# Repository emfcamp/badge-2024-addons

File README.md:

# EMF Badge Addons

Welcome!  This is the place to share your addons for the EMF 2024+ Badges.

## Addon submission rules

- Addons need to follow the top-level folder structure: `your_handle/addon_name/`
- We recommend you split your addon inside this folder into hardware and software (if needed) directories
- The top level of your addon folder should contain a README.md file, with a short description of the addon
- The top level of your addon folder should contain a photograph / render of your addon, in jpg or png format
- Addons in this repository are goverened by the repository license: CERN OHL Permissive. If you do not agree with this license, please don't submit your addon here.
- If your addon is a hexpansion, put hexpansion in the name so others can find it!

To submit your addon, open a pull request and we'll get it merged ASAP.  Pull requests will be minimally reviewed, mainly to make sure the rules are being followed.  Generally any update-PRs to a user's directory from that user will be accepted without much review.

Please don't make us make any more rules :D

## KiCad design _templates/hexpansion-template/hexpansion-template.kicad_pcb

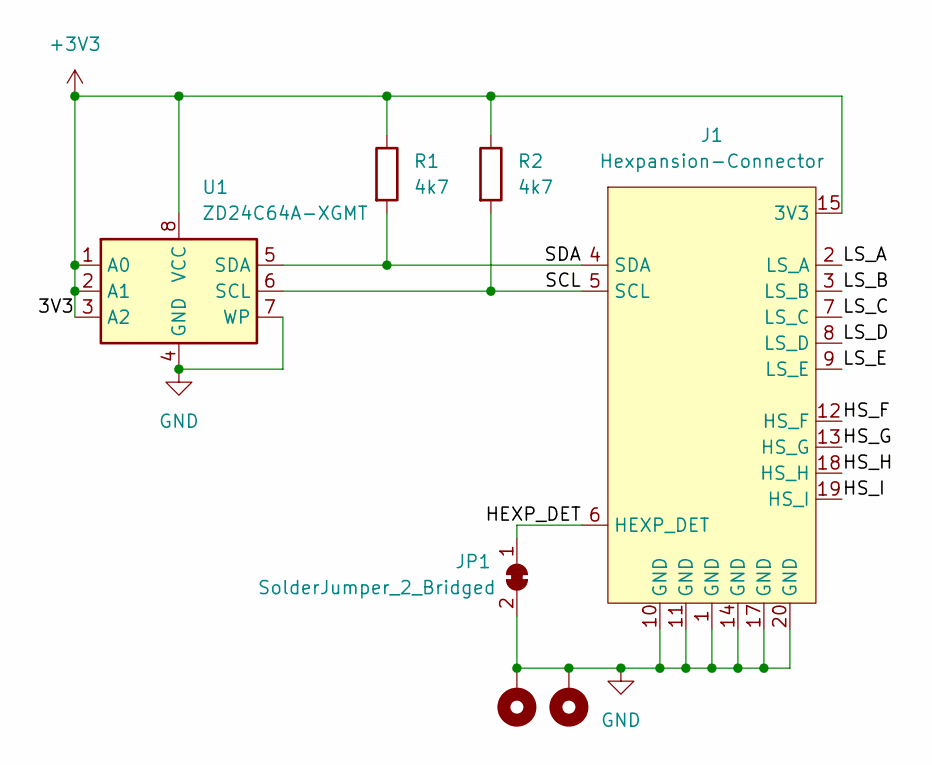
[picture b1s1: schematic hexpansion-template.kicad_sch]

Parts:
H1, H2: MountingHole_Pad; MountingHole_2.2mm_M2_Pad_Via
J1: Hexpansion-Connector; hexpansion-edge-connector
JP1: SolderJumper_2_Bridged; SolderJumper-2_P1.3mm_Bridged_RoundedPad1.0x1.5mm
R1, R2: 4k7; R_0402_1005Metric; MPN C5120109
U1: ZD24C64A-XGMT; TSSOP-8_4.4x3mm_P0.65mm; MPN C2875852

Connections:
+3V3: J1.15 (3V3), J1.16 (3V3), R1.1, R2.1, U1.1 (A0), U1.2 (A1), U1.3 (A2), U1.8 (VCC)
/HEXP_DET: J1.6 (HEXP_DET), JP1.1 (A)
/HS_F: J1.12 (HS_F)
/HS_G: J1.13 (HS_G)
/HS_H: J1.18 (HS_H)
/HS_I: J1.19 (HS_I)
/LS_A: J1.2 (LS_A)
/LS_B: J1.3 (LS_B)
/LS_C: J1.7 (LS_C)
/LS_D: J1.8 (LS_D)
/LS_E: J1.9 (LS_E)
/SCL: J1.5 (SCL), R2.2, U1.6 (SCL)
/SDA: J1.4 (SDA), R1.2, U1.5 (SDA)
GND: H1.1, H2.1, J1.1 (GND), J1.10 (GND), J1.11 (GND), J1.14 (GND), J1.17 (GND), J1.20 (GND), JP1.2 (B), U1.4 (GND), U1.7 (WP)

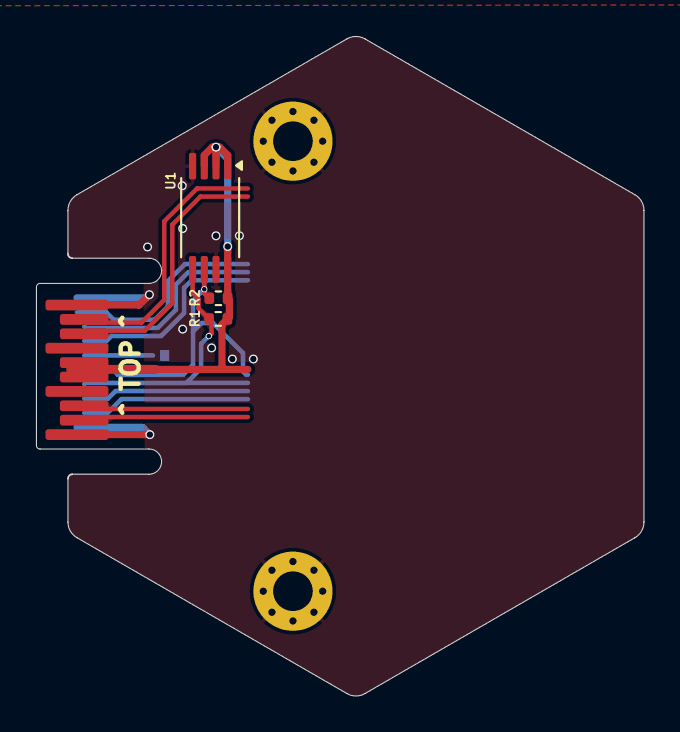
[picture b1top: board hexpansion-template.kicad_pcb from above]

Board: 2 copper layers, 33.7 x 36.6 mm, 7 parts (1 on the bottom side), 5 nets.

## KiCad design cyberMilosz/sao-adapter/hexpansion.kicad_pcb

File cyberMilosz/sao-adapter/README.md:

# SAOv2 / SAOv1.69bis hexpansion/hexdapter(?)

Provides power, `SDA`/`SCL` and exposes `LS_A`/`LS_B` as GPIO pins to your bog-standard [Simple Add-On](https://hackaday.io/project/175182-simple-add-ons-sao)/[Shitty Add-On](https://hackaday.com/2019/03/20/introducing-the-shitty-add-on-v1-69bis-standard/)

If everything goes to plan (does it ever?), this board should unleash the "power" of SAOs in the Tildragon.

wow!

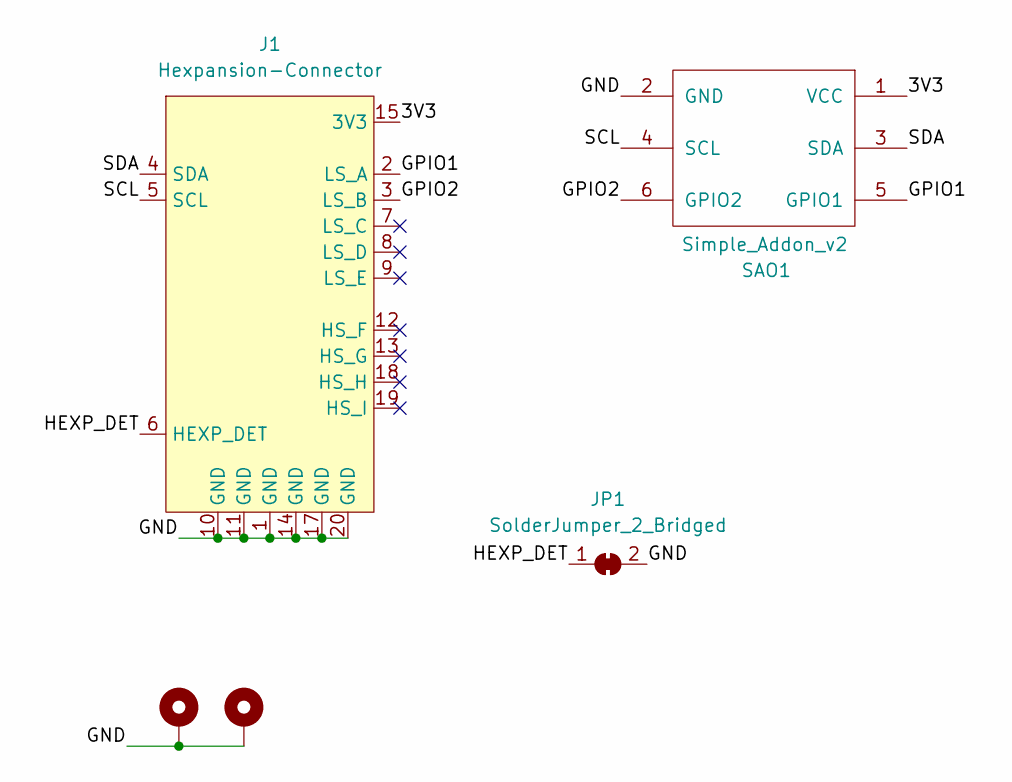
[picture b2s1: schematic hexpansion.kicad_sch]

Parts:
H1, H2: MountingHole_Pad; MountingHole_2.2mm_M2_Pad_Via
J1: Hexpansion-Connector; hexpansion-edge-connector
JP1: SolderJumper_2_Bridged; SolderJumper-2_P1.3mm_Bridged_RoundedPad1.0x1.5mm
SAO1: Simple_Addon_v2; Simple_Addon_v2-BADGE-2x3

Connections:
/3V3: J1.15 (3V3), J1.16 (3V3), SAO1.1 (VCC)
/GND: H1.1, H2.1, J1.1 (GND), J1.10 (GND), J1.11 (GND), J1.14 (GND), J1.17 (GND), J1.20 (GND), JP1.2 (B), SAO1.2 (GND)
/GPIO1: J1.2 (LS_A), SAO1.5 (GPIO1)
/GPIO2: J1.3 (LS_B), SAO1.6 (GPIO2)
/HEXP_DET: J1.6 (HEXP_DET), JP1.1 (A)
/SCL: J1.5 (SCL), SAO1.4 (SCL)
/SDA: J1.4 (SDA), SAO1.3 (SDA)

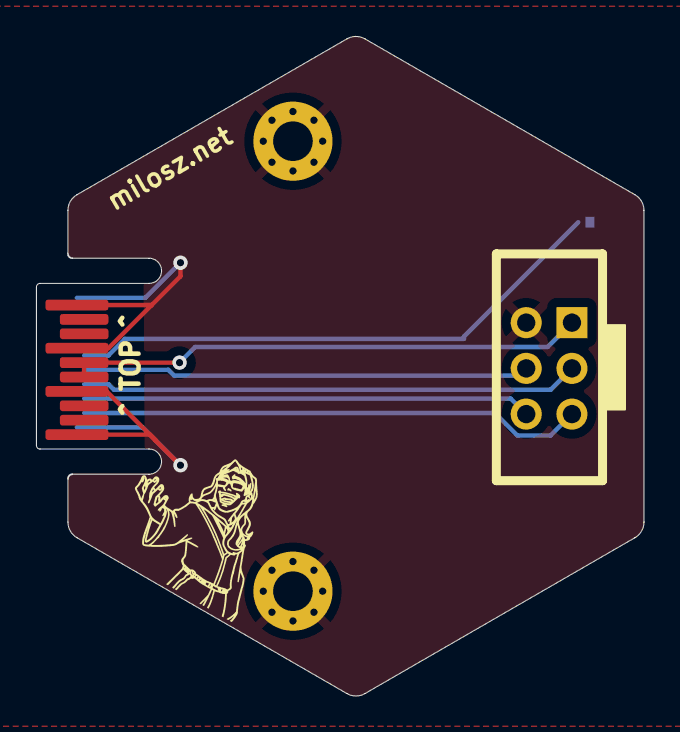
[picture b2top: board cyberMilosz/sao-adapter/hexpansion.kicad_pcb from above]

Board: 2 copper layers, 33.7 x 36.6 mm, 5 parts (1 on the bottom side), 7 nets.

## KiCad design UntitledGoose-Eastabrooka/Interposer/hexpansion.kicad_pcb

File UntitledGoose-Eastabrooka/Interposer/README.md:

# Nightmarket Interposer

### Attribution, Thanks, and Backstory. 

Well wasn't that a fun EMF 2024 !

Massive thanks to all on the Badge Team who answered questions of mine on Matrix, and in person. 

Specifically, Matthew Wilkes and Naomi Pentrel.

Another mention to @konichiwakitty who facilitated getting me a spot in the Nightmarket. 

It was my first time selling *Anything*, Let alone my own PCB's. 

I take great pride in the fact that I've been able to get helpful debugging tools into the hands of fellow EMF Attendees. 

### Original Source 

[The Original Breakout](https://github.com/emfcamp/badge-2024-hardware/tree/main/hexpansion)

### What you can do with it.

It has 3 purposes. 

1) Online HW without a Badge. 
2) Breakout SFP from the Badge to whatever you need. 
3) Interpose comms between badge and Hexpansions. 

### PCB Issues

I am not a PCB Designer by trade, this was part of the first few PCBs I have made in a long time. 

It may very well be there are some questionable routing decisions on this PCB, or Bugs. Feel free to fork it, and improve.

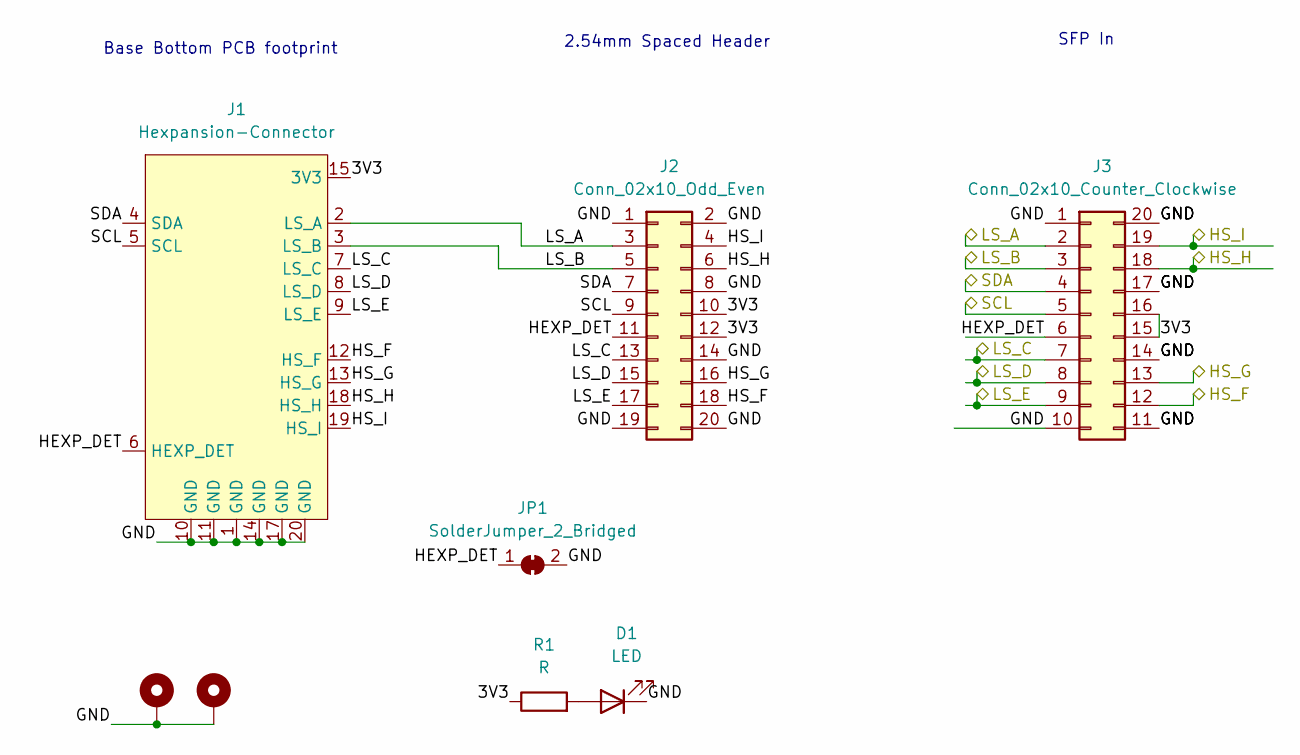
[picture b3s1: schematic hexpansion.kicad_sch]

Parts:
D1: LED; LED_0805_2012Metric
H1, H2: MountingHole_Pad; MountingHole_2.2mm_M2_Pad_Via
J1: Hexpansion-Connector; hexpansion-edge-connector
J2: Conn_02x10_Odd_Even; PinHeader_2x10_P2.54mm_Vertical
J3: Conn_02x10_Counter_Clockwise; SFP
JP1: SolderJumper_2_Bridged; SolderJumper-2_P1.3mm_Bridged_RoundedPad1.0x1.5mm
R1: R; R_0603_1608Metric

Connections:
/3V3: J1.15 (3V3), J1.16 (3V3), J2.10, J2.12, J3.15, J3.16, R1.1
/GND: D1.1 (K), H1.1, H2.1, J1.1 (GND), J1.10 (GND), J1.11 (GND), J1.14 (GND), J1.17 (GND), J1.20 (GND), J2.1, J2.2, J2.8, J2.14, J2.19, J2.20, J3.1, J3.10, J3.11, J3.14, J3.17, J3.20, JP1.2 (B)
/HEXP_DET: J1.6 (HEXP_DET), J2.11, J3.6, JP1.1 (A)
/HS_F: J1.12 (HS_F), J2.18, J3.12
/HS_G: J1.13 (HS_G), J2.16, J3.13
/HS_H: J1.18 (HS_H), J2.6, J3.18
/HS_I: J1.19 (HS_I), J2.4, J3.19
/LS_A: J1.2 (LS_A), J2.3, J3.2
/LS_B: J1.3 (LS_B), J2.5, J3.3
/LS_C: J1.7 (LS_C), J2.13, J3.7
/LS_D: J1.8 (LS_D), J2.15, J3.8
/LS_E: J1.9 (LS_E), J2.17, J3.9
/SCL: J1.5 (SCL), J2.9, J3.5
/SDA: J1.4 (SDA), J2.7, J3.4
unnamed: D1.2 (A), R1.2

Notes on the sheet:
2.54mm Spaced Header
SFP In
Base Bottom PCB footprint

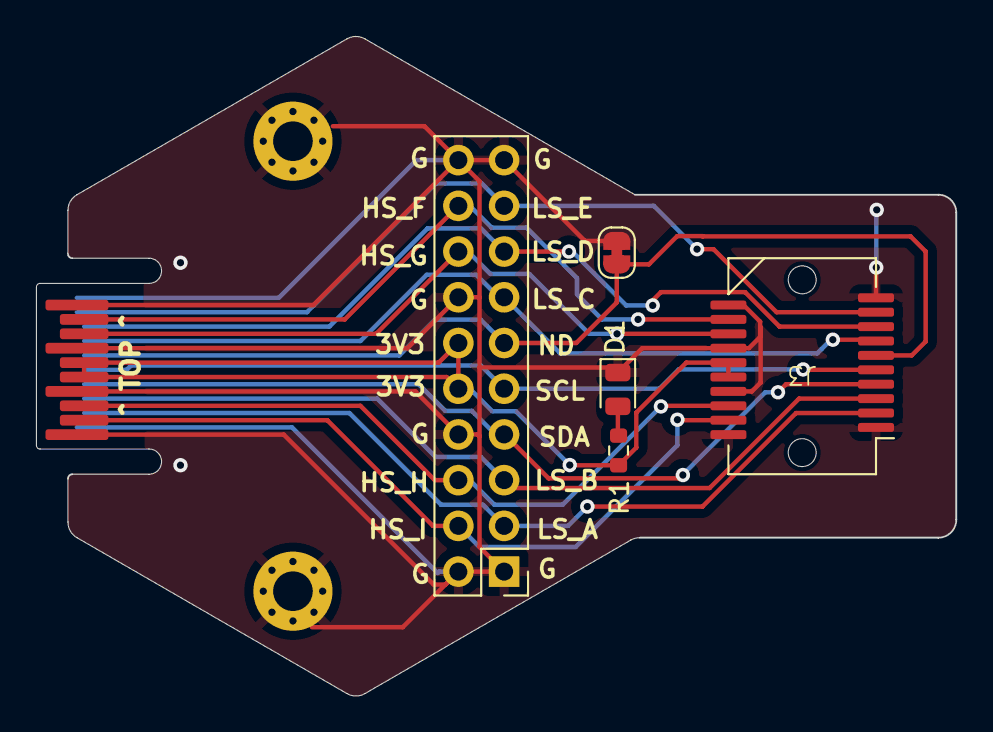
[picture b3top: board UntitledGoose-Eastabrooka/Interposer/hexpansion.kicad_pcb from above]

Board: 2 copper layers, 51.1 x 36.6 mm, 8 parts (0 on the bottom side), 15 nets.

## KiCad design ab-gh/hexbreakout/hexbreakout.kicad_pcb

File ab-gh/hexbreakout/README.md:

# Hexbreakout: Tildagon Hexpansion for Pimoroni Breakout Garden

This hexpansion addon is an adapter for [Pimoroni I2C Breakout Garden](https://shop.pimoroni.com/collections/electronics) boards. The source repo can be found [here](https://github.com/ab-gh/hexbreakout)

It simply connects 3v3, GND, SDA, and SCL, presenting them in the correct order for addons. It does not wire the interrupt pin. 

You can solder a 5-pin 2.54mm header pin, either vertical for short boards (BME280, SGP30) or right-angle for longer boards (MLX90640, 11x7 Matrix).

There are drilled slots for attachment holes.

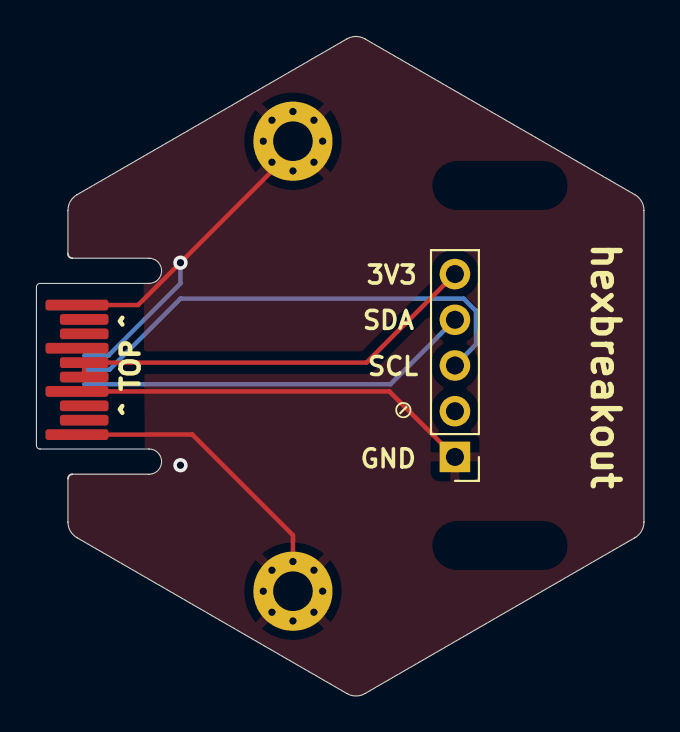
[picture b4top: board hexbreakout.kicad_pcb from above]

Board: 2 copper layers, 33.7 x 36.6 mm, 3 parts (0 on the bottom side), 2 nets.

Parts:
H1, H2: MountingHole_Pad; MountingHole_2.2mm_M2_Pad_Via
J1: Nodule-Connector; hexpansion-edge-connector

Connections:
/3V3: J1.15 (3V3), J1.16 (3V3)
/GND: H1.1, H2.1, J1.1 (GND), J1.6 (HEXP_DET), J1.10 (GND), J1.11 (GND), J1.14 (GND), J1.17 (GND), J1.20 (GND)

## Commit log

2024-03-19 Add license and readme
2024-03-19 adds ab-gh breakout garden
2024-03-28 v2 of googly eye hexpansion
2024-04-17 Add ap3602 to boost from 3v3 to 5v, as the minimum for the LEDs is 3.5v
2024-05-04 SAO adapter hexpansion
2024-05-25 Create tildagon-bumper-case
2024-05-25 Rename tildagon-bumper-case to readme.md
2024-06-01 Delete 3d-printable-case/EMF 2024 - Tildagon Bumper Badge - Screen Shim.stl
    Removed Old Screen Shim
2024-06-01 Add files via upload
    New Screen Shim, slightly larger and better clearence for surface mount components
2024-06-01 Update readme.md
    Reworded
2024-06-04 Interposer PCB
    Create a Branch / Commit for the Board that was made by me, and sold at the Nightmarket.
    It has 3 purposes.
    1) Online HW without a Badge.
    2) Breakout SFP from the Badge to whatever you need.
    3) Interpose comms between badge and Hexpansions.
2024-06-06 Goosepansion: Add goosepansion repository
2024-06-06 Goosepansion: update submodule
2024-07-20 Create Fusion360 Files for Tildagon Bumpers.
    Wanted to make modifying things easy for Fusion Users :)
2024-11-23 googly eye SW update
2024-11-23 Add hexpansion template
